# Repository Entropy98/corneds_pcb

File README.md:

# PCB for CorneDS 40% Keyboard

# TODO
## IO Board
 * Figure out IO
 * Add jumper to configure 5V/3.3V for joystick
 * Find 3.3V addressable LEDs
 * Add footprints for everything
 * Add 10k pullups to unused keys on keypad IC
 * Layout

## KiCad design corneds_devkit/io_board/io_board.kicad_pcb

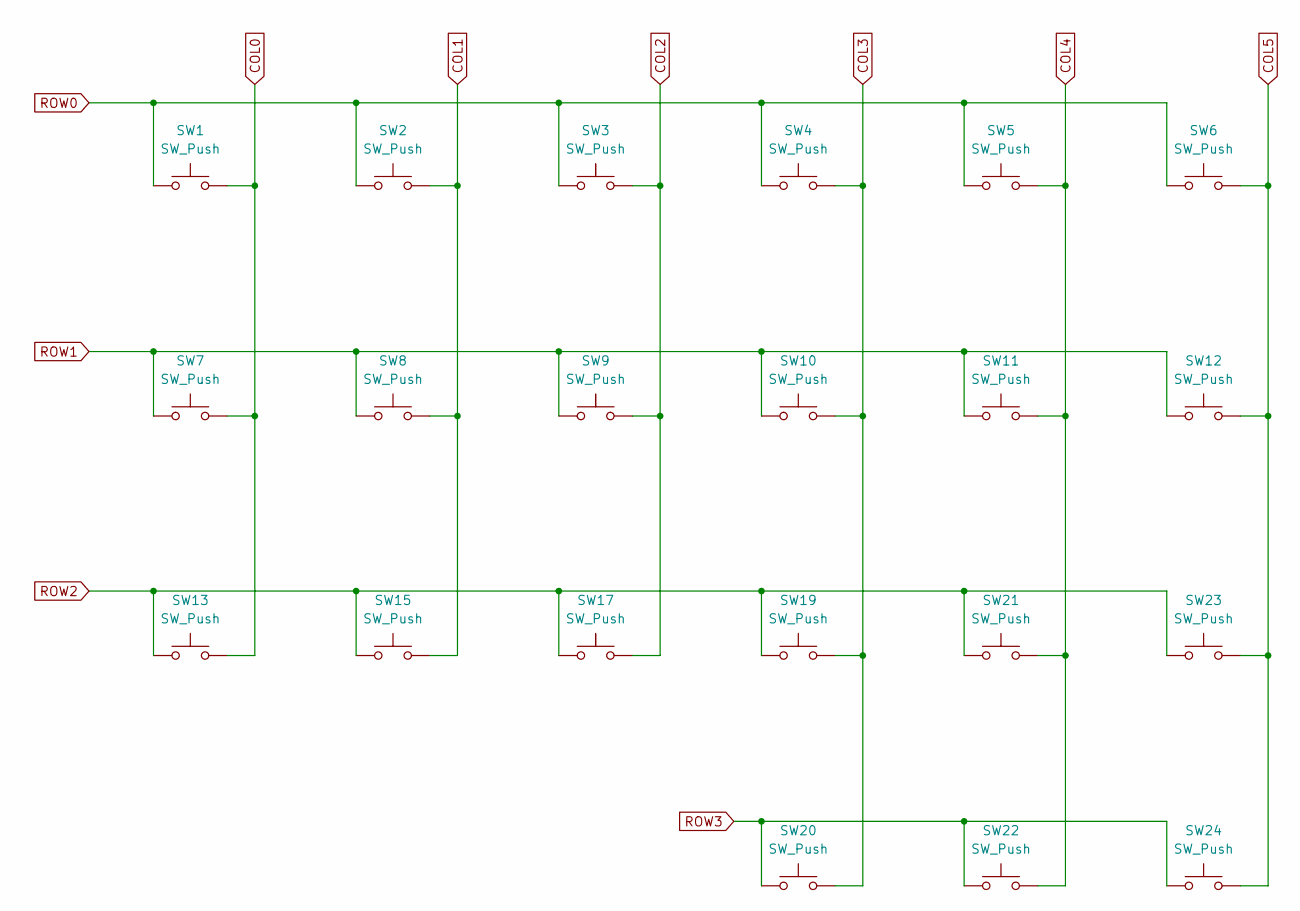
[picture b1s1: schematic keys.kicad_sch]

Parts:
SW1, SW2, SW3, SW4, SW5, SW6, SW7, SW8, SW9, SW10, SW11, SW12, SW13, SW15, SW17, SW19, SW20, SW21, SW22, SW23, SW24: SW_Push; SW_Gateron_LowProfile_HotSwap_PTH

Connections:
COL0: SW1.2, SW7.2, SW13.2; also elsewhere on the board
COL1: SW2.2, SW8.2, SW15.2; also elsewhere on the board
COL2: SW3.2, SW9.2, SW17.2; also elsewhere on the board
COL3: SW4.2, SW10.2, SW19.2, SW20.2; also elsewhere on the board
COL4: SW5.2, SW11.2, SW21.2, SW22.2; also elsewhere on the board
COL5: SW6.2, SW12.2, SW23.2, SW24.2; also elsewhere on the board
ROW0: SW1.1, SW2.1, SW3.1, SW4.1, SW5.1, SW6.1; also elsewhere on the board
ROW1: SW7.1, SW8.1, SW9.1, SW10.1, SW11.1, SW12.1; also elsewhere on the board
ROW2: SW13.1, SW15.1, SW17.1, SW19.1, SW21.1, SW23.1; also elsewhere on the board
ROW3: SW20.1, SW22.1, SW24.1; also elsewhere on the board

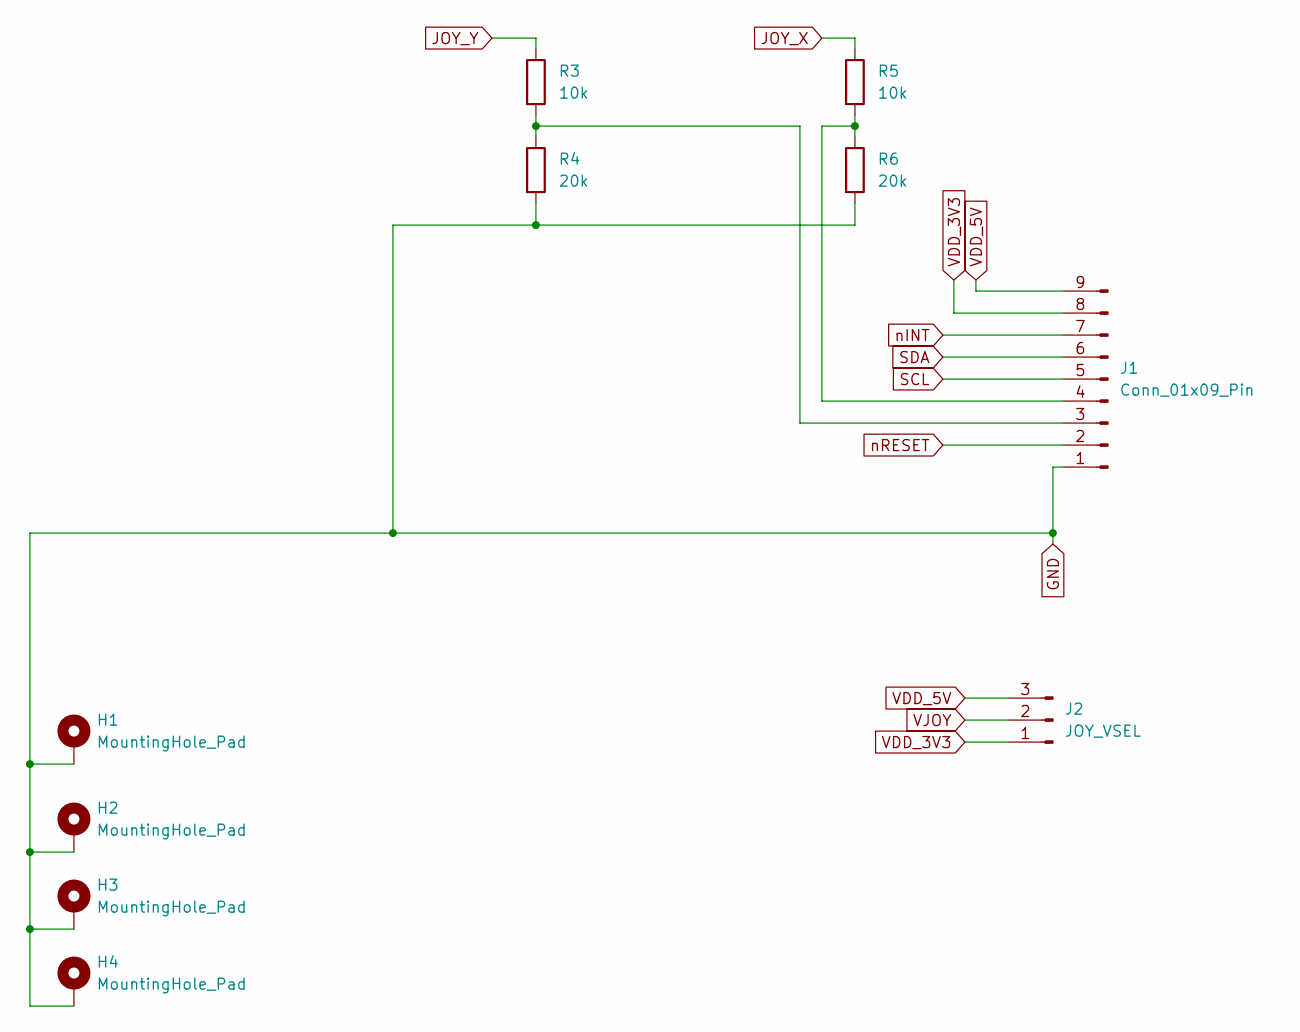
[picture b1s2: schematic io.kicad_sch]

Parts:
H1, H2, H3, H4: MountingHole_Pad; MountingHole_3.2mm_M3_Pad_Via
J1: Conn_01x09_Pin; PinSocket_1x09_P2.54mm_Vertical
J2: JOY_VSEL; PinSocket_1x03_P2.54mm_Vertical
R3, R5: 10k; R_0402_1005Metric
R4, R6: 20k; R_0402_1005Metric

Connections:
GND: H1.1 (1_1), H2.1 (1_1), H3.1 (1_1), H4.1 (1_1), J1.1, R4.2, R6.2; also elsewhere on the board
JOY_X: R5.1; also elsewhere on the board
JOY_Y: R3.1; also elsewhere on the board
unnamed: J1.3, R3.2, R4.1
unnamed: J1.4, R5.2, R6.1
SCL: J1.5; also elsewhere on the board
SDA: J1.6; also elsewhere on the board
VDD_3V3: J1.8, J2.1; also elsewhere on the board
VDD_5V: J1.9, J2.3
VJOY: J2.2; also elsewhere on the board
nINT: J1.7; also elsewhere on the board
nRESET: J1.2; also elsewhere on the board

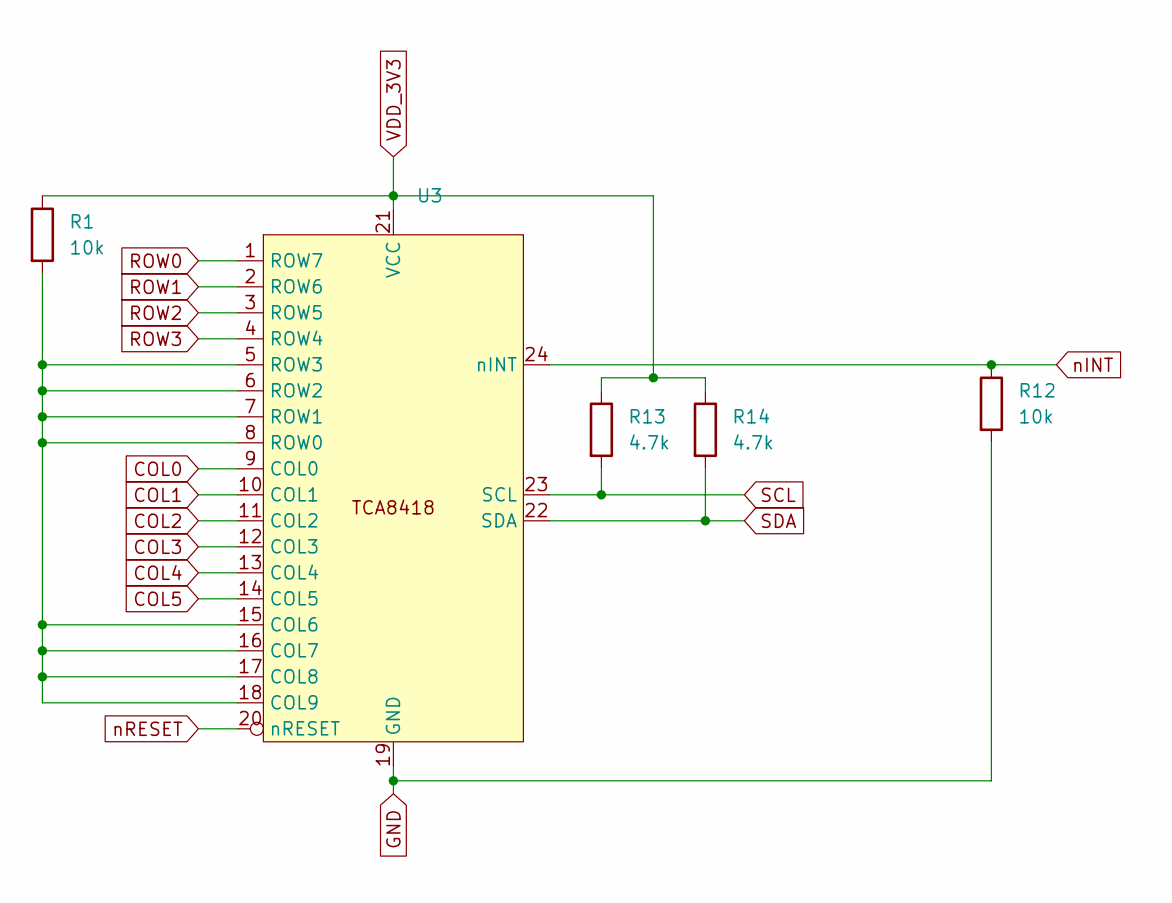
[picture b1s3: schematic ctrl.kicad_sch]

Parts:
R1, R12: 10k; R_0402_1005Metric
R13, R14: 4.7k; R_0402_1005Metric
U3: WQFN-24-1EP_4x4mm_P0.5mm_EP2.45x2.45mm

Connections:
COL0: U3.9 (COL0); also elsewhere on the board
COL1: U3.10 (COL1); also elsewhere on the board
COL2: U3.11 (COL2); also elsewhere on the board
COL3: U3.12 (COL3); also elsewhere on the board
COL4: U3.13 (COL4); also elsewhere on the board
COL5: U3.14 (COL5); also elsewhere on the board
GND: R12.2, U3.19 (GND); also elsewhere on the board
unnamed: R1.2, U3.5 (ROW3), U3.6 (ROW2), U3.7 (ROW1), U3.8 (ROW0), U3.15 (COL6), U3.16 (COL7), U3.17 (COL8), U3.18 (COL9)
ROW0: U3.1 (ROW7); also elsewhere on the board
ROW1: U3.2 (ROW6); also elsewhere on the board
ROW2: U3.3 (ROW5); also elsewhere on the board
ROW3: U3.4 (ROW4); also elsewhere on the board
SCL: R13.2, U3.23 (SCL); also elsewhere on the board
SDA: R14.2, U3.22 (SDA); also elsewhere on the board
VDD_3V3: R1.1, R13.1, R14.1, U3.21 (VCC); also elsewhere on the board
nINT: R12.1, U3.24 (nINT); also elsewhere on the board
nRESET: U3.20 (nRESET); also elsewhere on the board

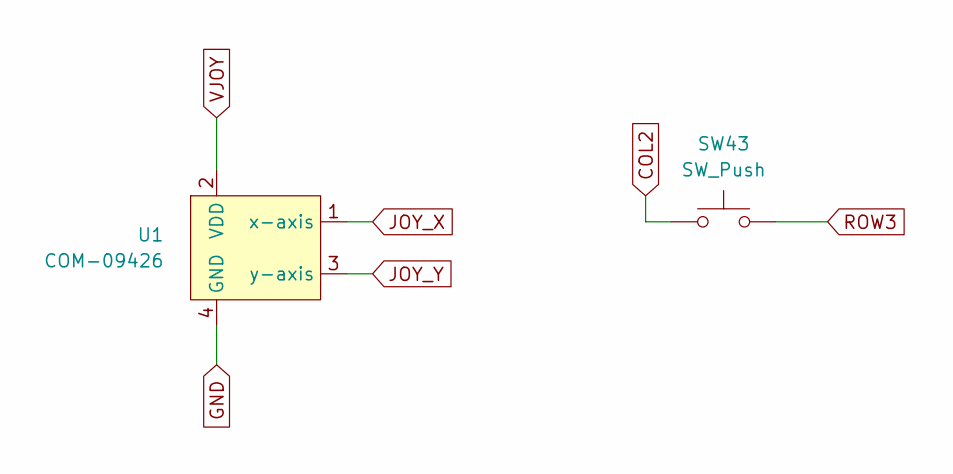
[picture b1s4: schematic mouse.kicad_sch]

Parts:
SW43: SW_Push; SW_Gateron_LowProfile_HotSwap_PTH
U1: COM-09426

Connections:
COL2: SW43.1; also elsewhere on the board
GND: U1.4 (GND); also elsewhere on the board
JOY_X: U1.1 (x-axis); also elsewhere on the board
JOY_Y: U1.3 (y-axis); also elsewhere on the board
ROW3: SW43.2; also elsewhere on the board
VJOY: U1.2 (VDD); also elsewhere on the board

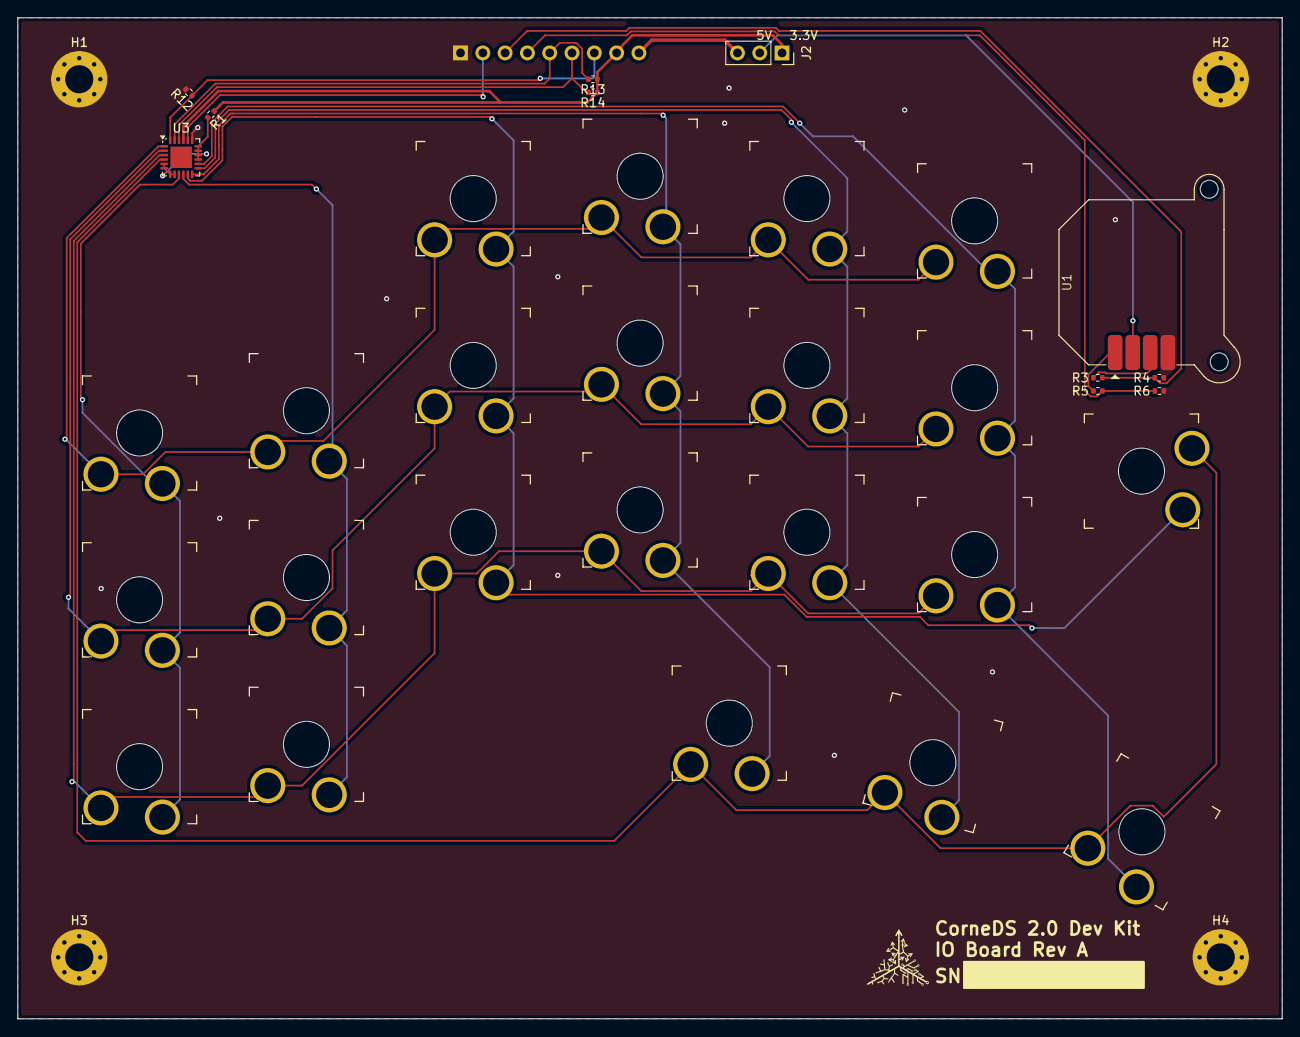
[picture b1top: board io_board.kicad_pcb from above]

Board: 2 copper layers, 144.0 x 114.0 mm, 38 parts (1 on the bottom side), 23 nets.

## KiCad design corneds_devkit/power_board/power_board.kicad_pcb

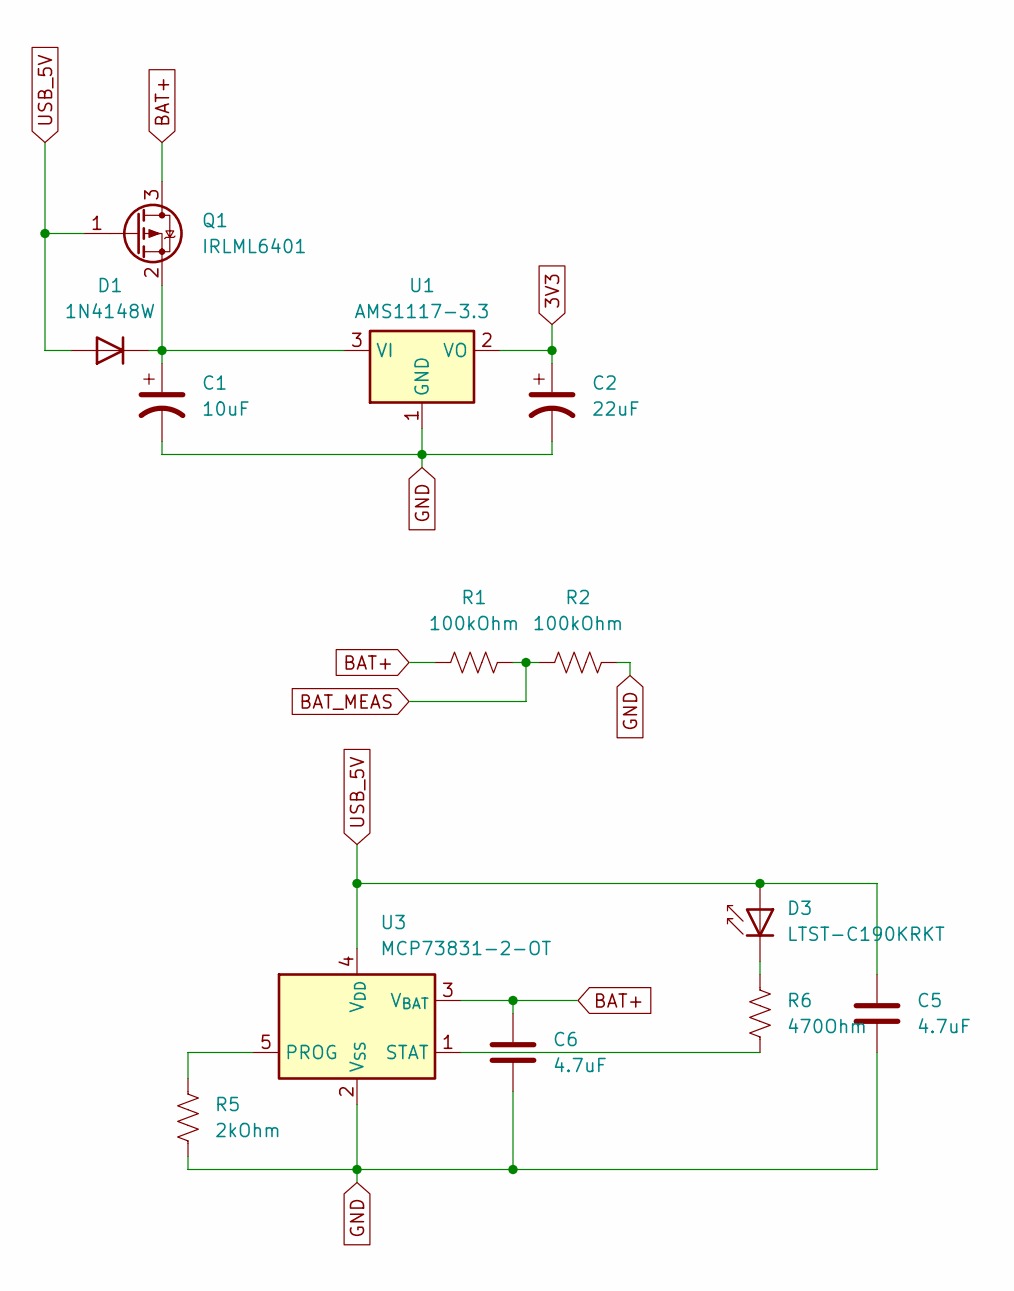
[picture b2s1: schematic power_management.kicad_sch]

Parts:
C1: 10uF; C_0402_1005Metric
C2: 22uF; C_0603_1608Metric
C5, C6: 4.7uF; C_0402_1005Metric
D1: 1N4148W; D_SOD-123
D3: LTST-C190KRKT; LED_0603_1608Metric
Q1: IRLML6401; SOT-23
R1, R2: 100kOhm; R_0402_1005Metric
R5: 2kOhm; R_0402_1005Metric
R6: 470Ohm; R_0402_1005Metric
U1: AMS1117-3.3; SOT-223-3_TabPin2
U3: MCP73831-2-OT; SOT-23-5

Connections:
3V3: C2.1, U1.2 (VO); also elsewhere on the board
BAT+: C6.1, Q1.3 (D), R1.1, U3.3 (V_{BAT}); also elsewhere on the board
BAT_MEAS: R1.2, R2.1; also elsewhere on the board
GND: C1.2, C2.2, C5.2, C6.2, R2.2, R5.1, U1.1 (GND), U3.2 (V_{SS}); also elsewhere on the board
unnamed: C1.1, D1.1 (K), Q1.2 (S), U1.3 (VI)
unnamed: D3.1 (K), R6.2
unnamed: R5.2, U3.5 (PROG)
unnamed: R6.1, U3.1 (STAT)
USB_5V: C5.1, D1.2 (A), D3.2 (A), Q1.1 (G), U3.4 (V_{DD}); also elsewhere on the board

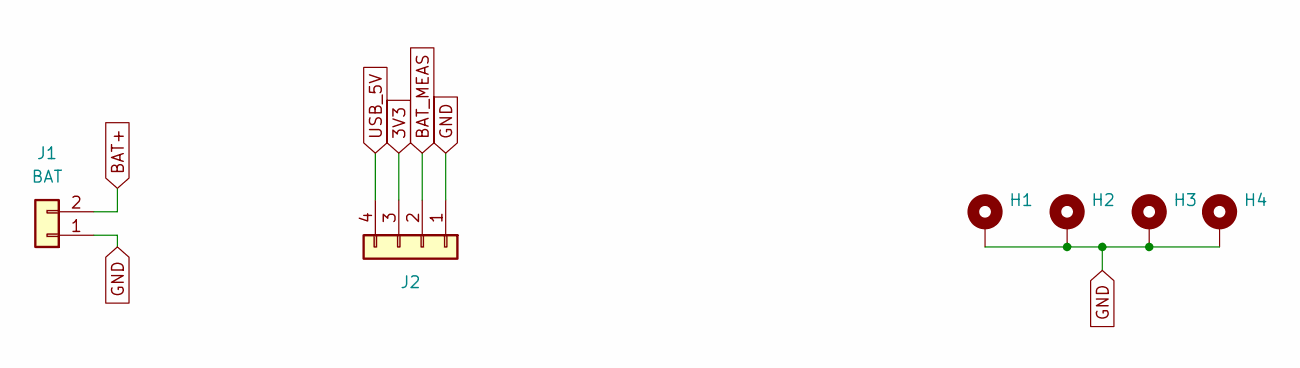
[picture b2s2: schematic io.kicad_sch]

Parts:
H1, H2, H3, H4: MountingHole_3.2mm_M3_Pad_Via
J1: BAT; JST_PH_S2B-PH-K_1x02_P2.00mm_Horizontal
J2: PinHeader_1x04_P1.27mm_Vertical

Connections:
3V3: J2.3; also elsewhere on the board
BAT+: J1.2; also elsewhere on the board
BAT_MEAS: J2.2; also elsewhere on the board
GND: H1.1, H2.1, H3.1, H4.1, J1.1, J2.1; also elsewhere on the board
USB_5V: J2.4; also elsewhere on the board

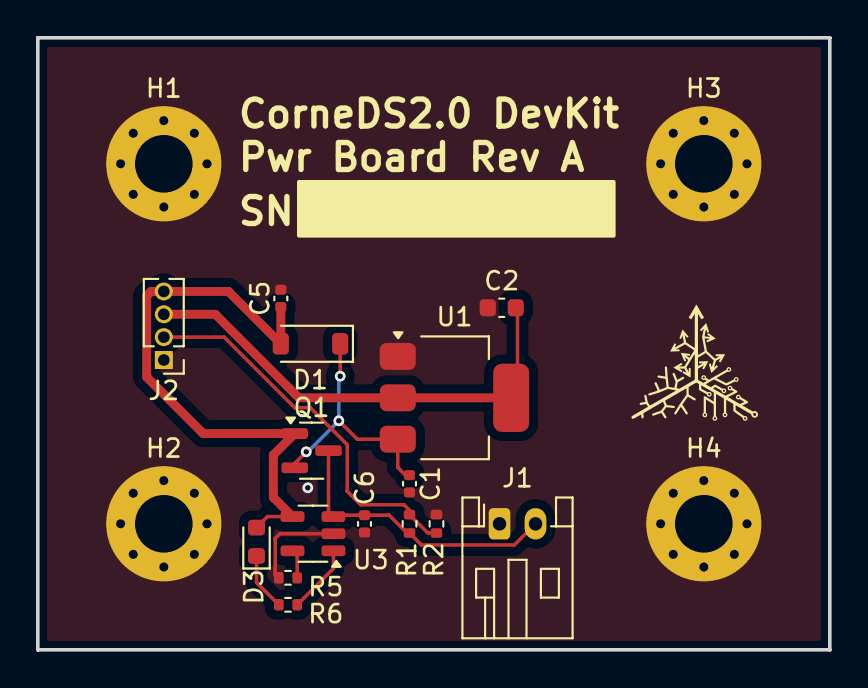
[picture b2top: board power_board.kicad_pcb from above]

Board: 2 copper layers, 44.0 x 34.0 mm, 19 parts (0 on the bottom side), 9 nets.

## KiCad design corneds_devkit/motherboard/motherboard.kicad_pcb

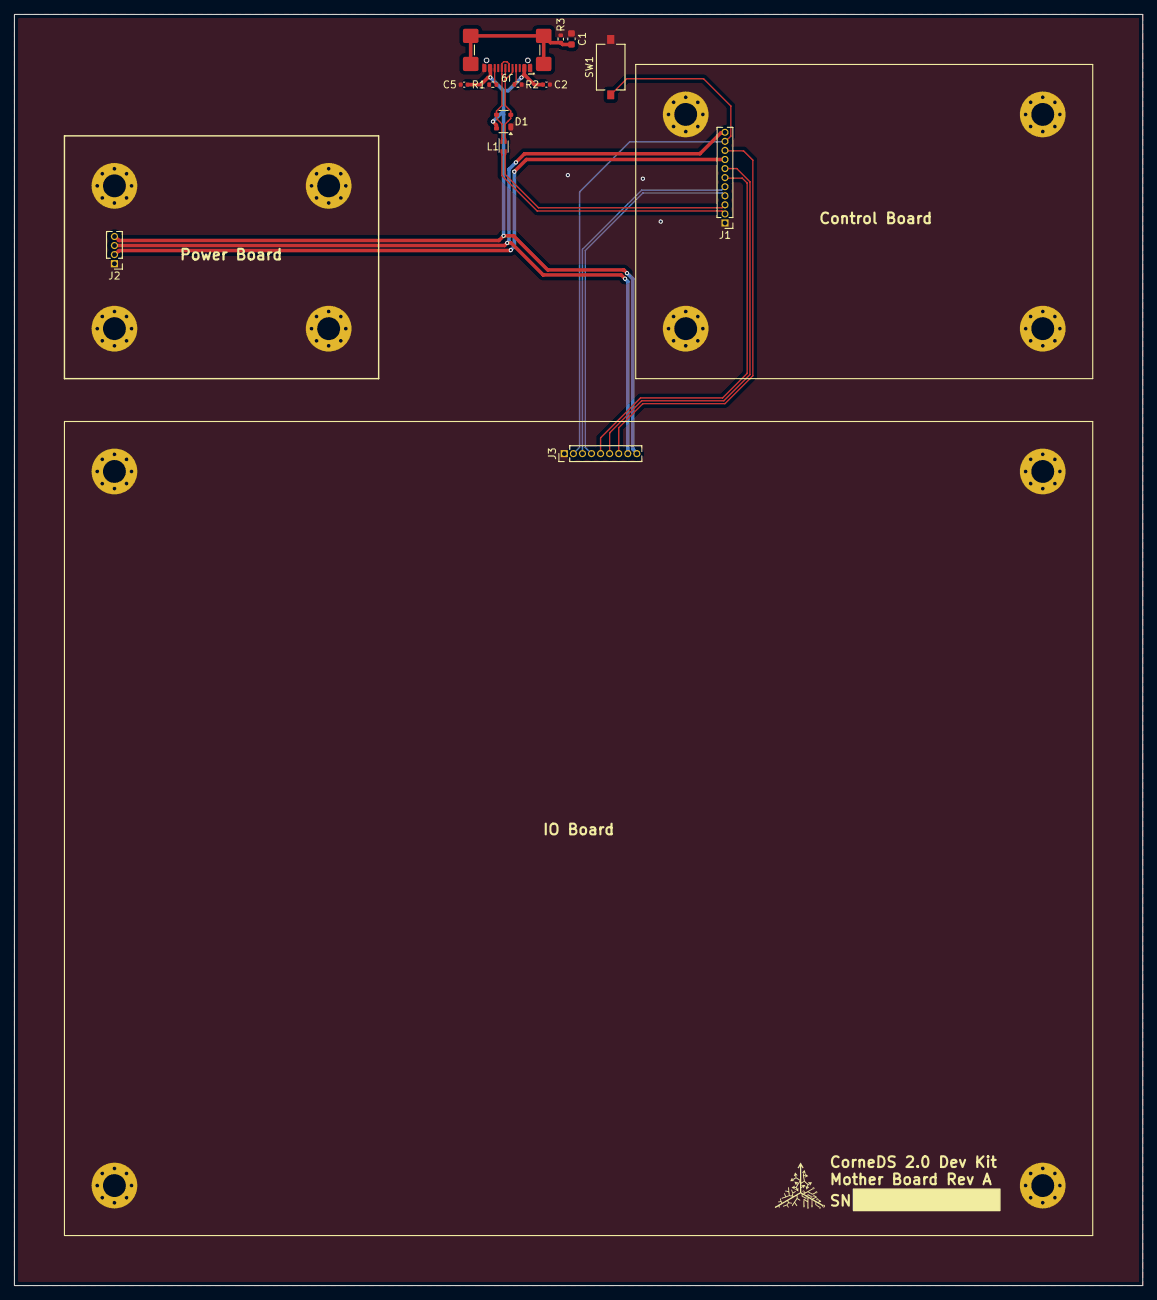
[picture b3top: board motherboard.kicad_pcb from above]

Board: 2 copper layers, 158.0 x 178.0 mm, 25 parts (0 on the bottom side), 17 nets.

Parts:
C1: 4.7nF; C_0603_1608Metric
C2: 10μF; C_0402_1005Metric
C5: 100nF; C_0402_1005Metric
D1: PRTR5V0U2X; SOT-143
H1, H2, H3, H4, H5, H6, H7, H8, H9, H10, H11, H12: MountingHole_3.2mm_M3_Pad_Via
J1: CTRL_BOARD; PinHeader_1x11_P1.27mm_Vertical
J2: PWR_BOARD; PinHeader_1x04_P1.27mm_Vertical
J3: IO_BOARD; PinHeader_1x09_P1.27mm_Vertical
J9: USB-C_2.0; USB_C_Receptacle_GCT_USB4110
L1: L_Iron_Coupled_1243; L_CommonModeChoke_Coilcraft_0603USB
R1, R2: 5.1kΩ; R_0402_1005Metric
R3: 1MΩ; R_0402_1005Metric
SW1: SW_Push; SW_Tactile_SPST_NO_Straight_CK_PTS636Sx25SMTRLFS

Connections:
3V3: J1.11, J2.3, J3.8
BAT_MEAS: J1.8, J2.2
D0+: D1.3 (IO2), J9.A6 (DP1), J9.B6 (DP2), L1.1
D0-: D1.2 (IO1), J9.A7 (DN1), J9.B7 (DN2), L1.4
D+: J1.2, L1.2
D-: J1.3, L1.3
GND: C1.2, C2.2, C5.2, D1.1 (GND), H1.1, H2.1, H3.1, H4.1, H5.1, H6.1, H7.1, H8.1, H9.1, H10.1, H11.1, H12.1, J1.1, J2.1, J3.1, J9.A1 (GND_A), J9.A12 (GND_A__1), J9.B1 (GND_B), J9.B12 (GND_B__1), R1.1, R2.1, R3.2, SW1.2
JOY_X: J1.4, J3.4
JOY_Y: J1.5, J3.3
unnamed: J9.A5 (CC1), R2.2
unnamed: J9.B5 (CC2), R1.2
unnamed: C1.1, J9.S1 (SHELL_GND), R3.1
SCL: J1.6, J3.5
SDA: J1.7, J3.6
USB_5V: C2.1, C5.1, D1.4 (VCC), J2.4, J3.9, J9.A4 (VBUS_A), J9.A9 (VBUS_A__1), J9.B4 (VBUS_B), J9.B9 (VBUS_B__1)
nKEY_INT: J1.9, J3.7
nRESET: J1.10, J3.2, SW1.1

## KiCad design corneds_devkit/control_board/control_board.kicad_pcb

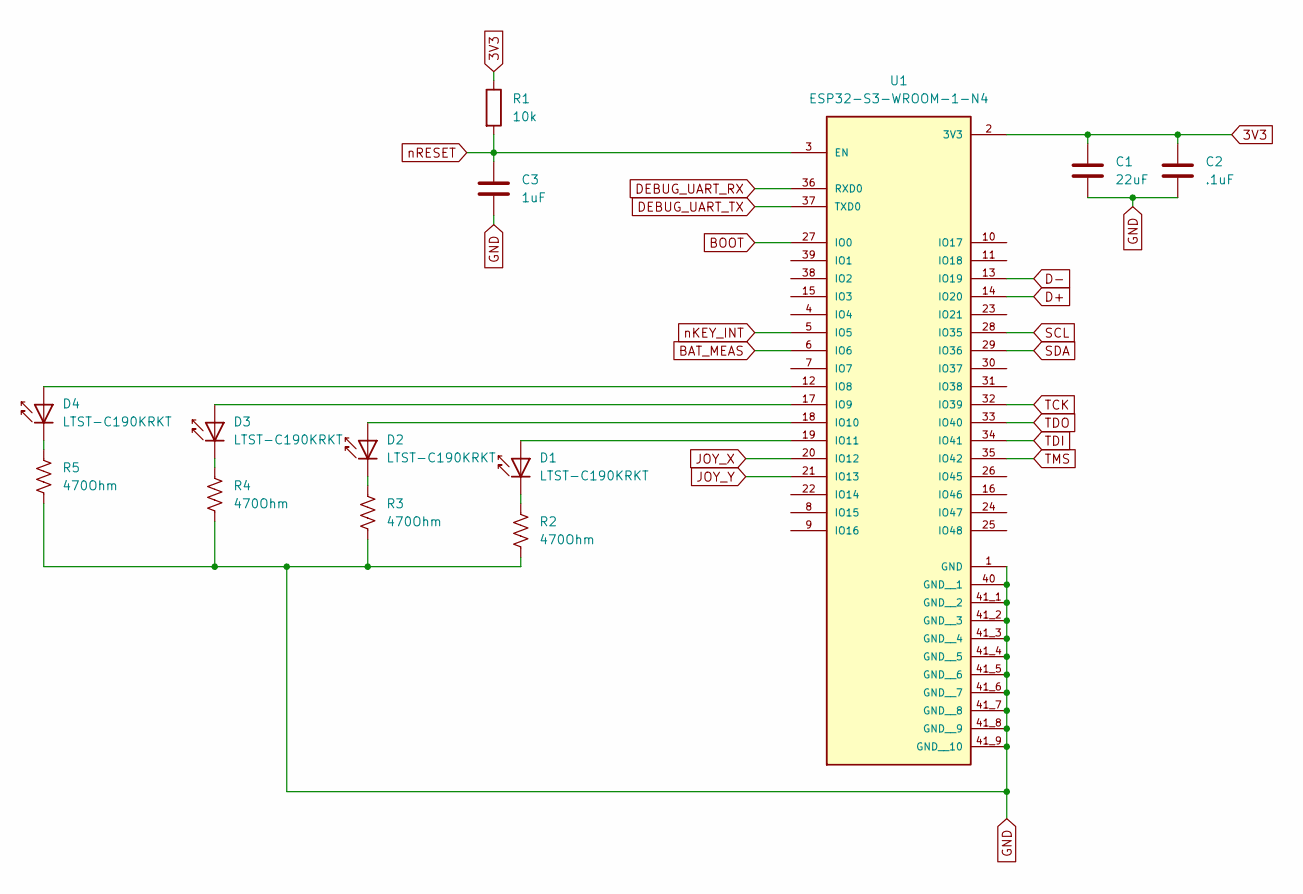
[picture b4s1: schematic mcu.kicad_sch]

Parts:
C1: 22uF; C_0603_1608Metric
C2: .1uF; C_0402_1005Metric
C3: 1uF; C_0402_1005Metric
D1, D2, D3, D4: LTST-C190KRKT; LED_0603_1608Metric
R1: 10k; R_0402_1005Metric
R2, R3, R4, R5: 470Ohm; R_0402_1005Metric
U1: ESP32-S3-WROOM-1-N4; XCVR_ESP32-S3-WROOM-1-N4; PARTREV v1.0

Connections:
3V3: C1.1, C2.1, R1.1, U1.2 (3V3); also elsewhere on the board
BAT_MEAS: U1.6 (IO6); also elsewhere on the board
BOOT: U1.27 (IO0); also elsewhere on the board
D+: U1.14 (IO20); also elsewhere on the board
D-: U1.13 (IO19); also elsewhere on the board
DEBUG_UART_RX: U1.36 (RXD0); also elsewhere on the board
DEBUG_UART_TX: U1.37 (TXD0); also elsewhere on the board
GND: C1.2, C2.2, C3.2, R2.1, R3.1, R4.1, R5.1, U1.1 (GND), U1.40 (GND__1), U1.41_1 (GND__2), U1.41_2 (GND__3), U1.41_3 (GND__4), U1.41_4 (GND__5), U1.41_5 (GND__6), U1.41_6 (GND__7), U1.41_7 (GND__8), U1.41_8 (GND__9), U1.41_9 (GND__10), U1.GND; also elsewhere on the board
JOY_X: U1.20 (IO12); also elsewhere on the board
JOY_Y: U1.21 (IO13); also elsewhere on the board
unnamed: D1.2 (A), U1.19 (IO11)
unnamed: D1.1 (K), R2.2
unnamed: D2.2 (A), U1.18 (IO10)
unnamed: D2.1 (K), R3.2
unnamed: D3.2 (A), U1.17 (IO9)
unnamed: D3.1 (K), R4.2
unnamed: D4.2 (A), U1.12 (IO8)
unnamed: D4.1 (K), R5.2
SCL: U1.28 (IO35); also elsewhere on the board
SDA: U1.29 (IO36); also elsewhere on the board
TCK: U1.32 (IO39); also elsewhere on the board
TDI: U1.34 (IO41); also elsewhere on the board
TDO: U1.33 (IO40); also elsewhere on the board
TMS: U1.35 (IO42); also elsewhere on the board
nKEY_INT: U1.5 (IO5); also elsewhere on the board
nRESET: C3.1, R1.2, U1.3 (EN); also elsewhere on the board

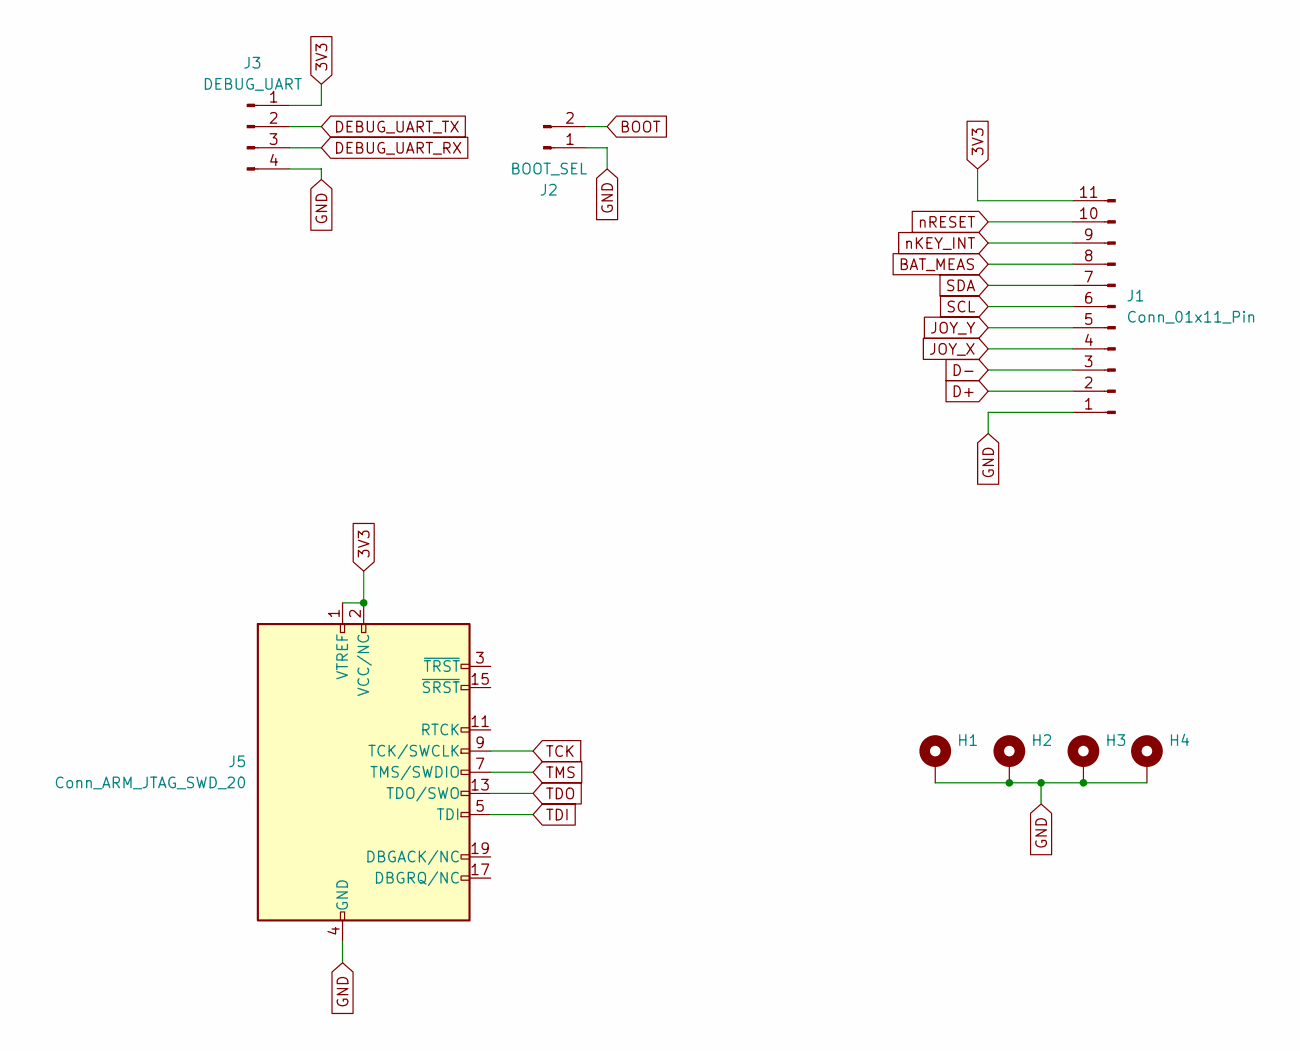
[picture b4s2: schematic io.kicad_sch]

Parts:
H1, H2, H3, H4: MountingHole_3.2mm_M3_Pad_Via
J1: Conn_01x11_Pin; PinHeader_1x11_P1.27mm_Vertical
J2: BOOT_SEL; PinHeader_1x02_P1.27mm_Vertical
J3: DEBUG_UART; PinHeader_1x04_P1.27mm_Vertical
J5: Conn_ARM_JTAG_SWD_20; CONN_7024620xx_MOL

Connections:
3V3: J1.11, J3.1, J5.1 (VTREF), J5.2 (VCC/NC); also elsewhere on the board
BAT_MEAS: J1.8; also elsewhere on the board
BOOT: J2.2; also elsewhere on the board
D+: J1.2; also elsewhere on the board
D-: J1.3; also elsewhere on the board
DEBUG_UART_RX: J3.3; also elsewhere on the board
DEBUG_UART_TX: J3.2; also elsewhere on the board
GND: H1.1, H2.1, H3.1, H4.1, J1.1, J2.1, J3.4, J5.4 (GND), J5.6 (GND), J5.8 (GND), J5.10 (GND), J5.12 (GND), J5.14 (GND), J5.16 (GND), J5.18 (GND), J5.20 (GND); also elsewhere on the board
JOY_X: J1.4; also elsewhere on the board
JOY_Y: J1.5; also elsewhere on the board
SCL: J1.6; also elsewhere on the board
SDA: J1.7; also elsewhere on the board
TCK: J5.9 (TCK/SWCLK); also elsewhere on the board
TDI: J5.5 (TDI); also elsewhere on the board
TDO: J5.13 (TDO/SWO); also elsewhere on the board
TMS: J5.7 (TMS/SWDIO); also elsewhere on the board
nKEY_INT: J1.9; also elsewhere on the board
nRESET: J1.10; also elsewhere on the board

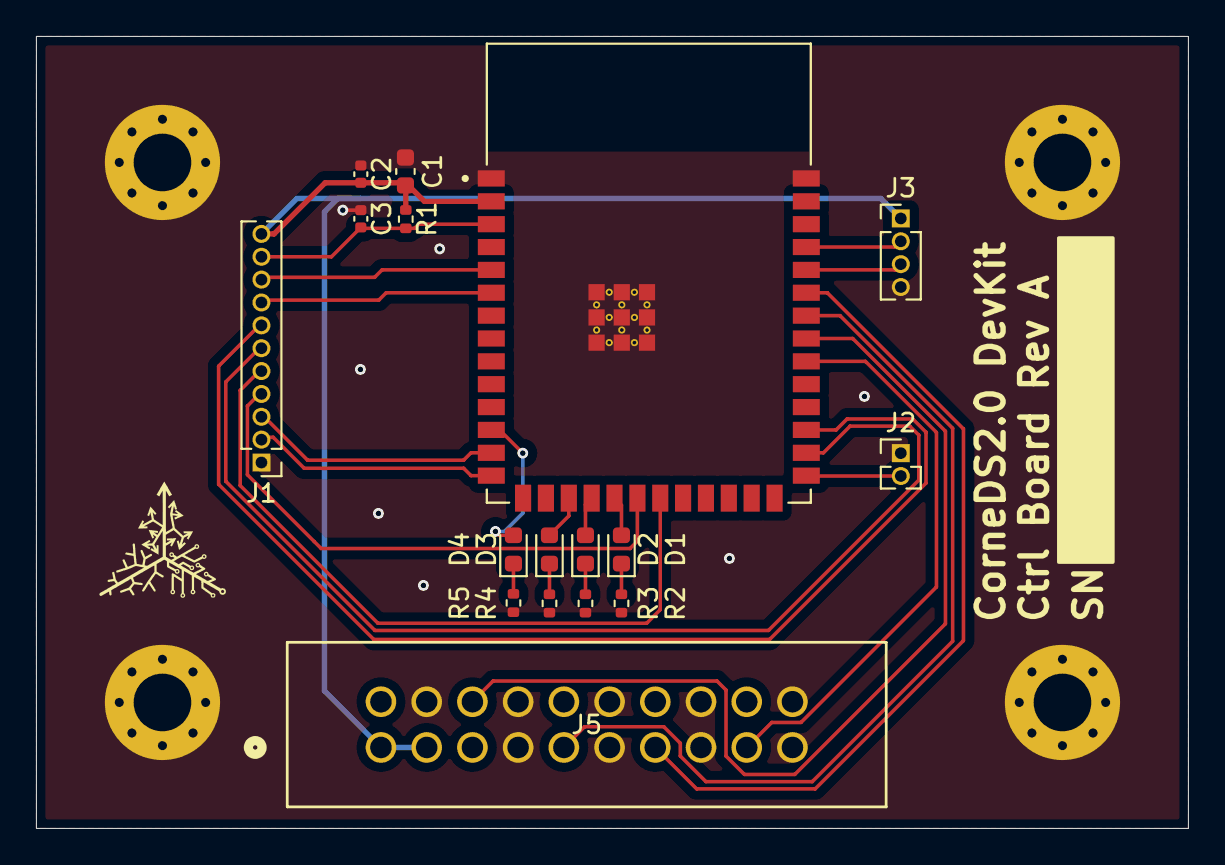
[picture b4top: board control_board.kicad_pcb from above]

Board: 2 copper layers, 64.0 x 44.0 mm, 21 parts (0 on the bottom side), 26 nets.

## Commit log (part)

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2024-01-06 seperating pcb files into submodule
2024-01-10 removed cols and rows on key switches in sch
2024-05-15 not sure what these uncommited changes are
2024-05-16 started on bom and schematic for devkit motherboard
2024-09-02 started on io board schematic
2024-09-02 finished key boards
2024-09-03 finished mouse and key boards
2024-09-03 finished schematic for io board
2024-09-03 started working on power board
2024-09-04 removed nucleo board because we're not using that mcu anymore and started control board
2024-09-13 working on usbc and power
2025-03-01 re-routed io board with keypad IC
2025-03-07 added switch footprint, io sch, and keypad IC footprint. Need to find new LEDs and make joystick footprint
2025-03-08 io sch done. Need to route
2025-03-12 routing left keys pcb
2025-03-13 finished io board
2025-03-14 made power schematic and started on routing power board
2025-03-14 finished routing power board and started on control board schematic but realized I need seperate reset lines
2025-08-04 ordered devkit rev A
